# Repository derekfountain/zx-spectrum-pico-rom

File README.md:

# zx-spectrum-pico-rom

## A Pico-based switchable ROM interface for the ZX Spectrum

This is a ROM interface board for the ZX Spectrum. It presents a new,
selectable ROM image for the machine, replacing the 1982 BASIC one
found in the IC on the Spectrum's PCB.

There are lots of these around, all based on ROM and EEPROM chips. My
design is based on a Raspberry Pi Pico microcontroller programmed to
emulate a ROM chip.

The main advantage of doing it this way is that the Pico has enough
memory for several ROM images, and enough flash for as many ROMs as
anyone would likely ever want. A button allows the loaded ROMs to be
cycled.

It works like this (click through for YouTube video):

https://youtube.com/shorts/0Ot5mol2f5A?feature=share

Update Dec'24: I used this Pico ROM project as the basis for a bit
of experimentation with the Z80's non maskable interrupt (NMI) on 
the Spectrum. Updated software and description are [here](https://github.com/derekfountain/zx-spectrum-pico-rom/tree/main/firmware_nmi).
If you're after a simpler version of the Pico code to do a simple
ROM emulation task, that's probably the version you want.

Update Feb'25: I further used this Pico ROM project as the basis for adding a carefully timed non maskable interrupt (NMI) which fires each frame at the point the Spectrum is about to draw the lower border. Not sure how much value there is there, but if anyone's interested the subproject is [here](https://github.com/derekfountain/zx-spectrum-pico-rom/tree/main/firmware_nmi_lower_border).

## Design

The Z80's address and data bus lines are connected to the Pico's
GPIOs.  GPIOs are limited on the Pico (there's only 26), so only 14 of
the 16 address lines are connected. A bit of external logic handles the
top two. The software on the Pico sits spinning, watching for that logic
to indicate that A14, A15 and /MREQ are all zero, that being the indication
of a ZX Spectrum ROM memory access by the Z80. When that condition is
met the address the Z80 is requesting (in the range 0x0000 to 0x3FFF)
is found from the GPIOs connected to the address bus, and the value from
that offset in the currently enabled ROM image is fetched. The 8 bits of
that value are placed on the 8 GPIOs connected as outputs to the Z80's
data bus.

## Hardware design

The Spectrum is +5V, the Pico is 3V3, so every bus or signal pin needs
level shifting, down on the way into the Pico, up on the way out.

GPIO count is also pretty tight, which is why the external logic is
required. It's a simple 3-input OR gate which ORs A14, A15 and
/MREQ. The output of that gate is fed into the Pico, saving 2 GPIOs.

It's important that the device doesn't assert an output value onto the
Z80's data bus until it needs to. This is controlled by hardware. The
data bus level shifter is set permanently to the Pico->ZX direction,
but is left off (via its chip-enable line) until the ROM is being
read. The /CE line is pulled low by the output of the 3-way OR gate,
so when the Z80 is reading from ROM the level shifter is turned on and
the value on the data bus is connected to the Z80. As soon as the
/MREQ line goes high again the OR result goes true and the level shifter
is turned off again.

The Pico needs the ability to reset the Z80, which gets very unhappy if
the ROM program it's running is suddenly changed from underneath it. The
Z80's /RESET line is connected to a GPIO via a transistor; the line is
pulled low via Pico software when the Pico changes the ROM image in order
to reset the Z80.

There's a single user input button connected to the one remaining GPIO
on the Pico. In the current software this cycles the ROM to the next one
in the (compiled in) sequence. The Pico's ADC is available so more buttons
and a better user interface could be constructed using a resistor ladder.

The Z80's /M1 line is connected to a Pico GPIO input. This isn't required
for the typical use case, but it makes the device a useful test bed for
running the ZX Interface One ROM - see below.

### Caveat

Feb'25: I was playing around with one of these interfaces, and found myself
wanting to re-enable the Spectrum's ROM with the interface still plugged in.
(I needed the Pico for something, but with the Spectrum's own ROM.) So I
cut the /ROMCS track on the back of the interface, and then spent some time
trying to figure out why the Spectrum wasn't working.

Eventually it dawned on me: when I cut the track the Spectrum's ROM IC
was re-enabled, and it started to drive the data bus. But the U4 level
shifter was still working on the interface, which meant that was also driving
the data bus. That's a bad thing, the two ICs were both trying to be outputs
and were driving each other's data lines. The Z80 was getting garbage on the
data bus, and I think I was rather lucky nothing got damaged. I removed the
level shifter to complete my experimentation.

So, um, don't do that. :)

### Construction

The gerbers archive for upload, for example, JLCPCB, is
srom/fab1.2/fab1.2.zip. It's a simple 2 layer board.

Note: As of this writing I've not actually had one of these made. I
hand-modified my v1.1 board with the errata from v1.1. The v1.2 design
has had those modifications added so I'd expect it to work exactly the
same as my modified v1.1 board. But I haven't tried it yet. The switch,
in particular, might yet require another tweak depending on what
piece of hardware is chosen. I used a 6mm x 6mm right angle switch.

There's nothing complicated about the soldering. Do the big ICs first
and the Pico sockets, if you use them, last.

## Software Design

The software which runs on the Pico is built on a simple loop which
does this:

 * spin, waiting for the ROM-being-accessed signal to come in
 * read the 14 bits of the address bus from the GPIOs
 * convert that bit pattern into an offset
 * find the value of the byte at that offset into the currently
   used ROM image
 * apply the 8 bits of that byte value to the 8 output GPIOs connected
   to the Z80's data bus
 * go back to the top

The glaring issue here is speed. Pg8 of the Z80 manual says that the
timing for M1, the instruction fetch, is most time critical. The data
is sampled off the bus one and a half clocks after /MREQ goes low. On
the Spectrum's 3.5MHz Z80 that's 4.28571428571e-07 seconds, so about
430ns. Despite several efforts at optimisation I've been unable to get
the Pico to reliably return the data value inside that time frame. Much
to my frustration, v1.2 of the software still requires an overclock from
133MHz to 140MHz.

The Z80 starts up faster than the Pico which requires half a second or
so to get going. This means the Z80 is asking for ROM instructions 
before the Pico is ready to provide them. The Pico resets the Z80 as
soon as it, the Pico, is ready to go. That's why there's a colourful
display of randomness for a moment at startup.

## ROM Images

The device is permanently enabled; the original ROM chip in the
Spectrum is disabled while the interface is attached.

The Pico software contains the ROM images it's compiled with, the
first of which would typically be the original ZX ROM from 1982. I've
added a diagnostics ROM and the Gosh Wonderful ROM since they are free
to redistribute. Games ROMs are not included in the source release but
they can be added fairly easily. A Linux command like:

 xxd -i spaceraiders.rom

will convert a ROM image into 'C' array data which can be dropped into
roms.h.

### Switcher ROM

Some of the ROMs look superficially similar, like the original 1982
ROM and the Gosh Wonderful ROM. It got confusing trying to work out
what was running. I wanted a row of LEDs across the top of the device
to act as an indicator of which ROM was in use, but I didn't have any
GPIOs to implement it with. So I added an extra ROM image I called the
"switcher" ROM.

This program is written in 'C' and compiled with Z88DK. The source is
in the firmware/switcher directory. It presents a banner saying what ROM
is coming up next, then sits indefinitely buzzing the Spectrum's border.

")

When the user input button is pressed, the Pico software selects this
switcher ROM and resets the Z80 to start it running. The banner appears
on the Spectrum screen. About a second later an alarm goes off in the
Pico, the handler for which selects the next ROM in sequence and resets
the Z80 again. Thus the switcher ROM appears as a banner on the Spectrum
screen between each ROM switch.

## ZX Interface One

This device can also switch in and out the ZX Interface One's ROM. This
is an 8K ROM which, in the actual IF1, is paged in by hardware on 3 magic
address accesses: it's paged in when the Z80 requests an instruction from
addresses 0x0008 and 0x1708, and paged out again when the Z80 requests an
instruction from address 0x0700. It's early days with this idea, but that
boils down to this code:

    if( (rom_address == 0x0008) || (rom_address == 0x1708) )
    {
      rom_image_ptr = __ROMs_if1_rom;
    }
    else if( rom_address == 0x0700 )
    {
      rom_image_ptr = __ROMs_48_original_rom;
    }

This needs the /M1 input merged into the logic, but that's the
idea. The joys of programmable devices like the Pico, as opposed to
hardware. :)

There's a macro in the firmware source to switch in an early IF1 paging
version of the code. It seems unreliable, but I won't be persuing this
any further with this project.

Note: the v1.1 board doesn't have the /M1 signal connected. The v1.2
board has it connected into GPIO15. The software doesn't have the /M1
signal taken into account as yet.

## Bill of Materials

You will need:

3x [74LVC245 Bus transceiver](https://www.mouser.co.uk/ProductDetail/595-SN74LVC245ANSR)
Bus transceiver, used as a level shifter
<br>
1x [3216 SMD Diode](https://www.mouser.co.uk/ProductDetail/581-SD1206S040S2R0)
Schottky Diode for Pico input protection
<br>
1x [4075 OR gate](https://www.mouser.co.uk/ProductDetail/595-SN74HCS4075DR)
3-way 3-input OR gate
<br>
4x [3216 SMD 0.1uF capacitor](https://www.mouser.co.uk/ProductDetail/581-12065C104KAT4A)
Decoupling capacitor
<br>
1x [PMBT2222A SMD Transistor](https://www.mouser.co.uk/ProductDetail/771-PMBT2222A-T-R)
NPN Transistor for /RESET
<br>
1x [3216 SMD 1K Resistor](https://www.mouser.co.uk/ProductDetail/603-RT1206FRE071KL)
1K Resistor for /RESET

Also:

1x Raspberry Pi Pico with pins and sockets if you want them
<br>
1x ZX Spectrum Edge Connector socket
<br>
1x SPST switch any single pole, single throw switch to use as an input button. The footprint
on the board matches one I happen to have had, assume you'll add it on flying leads.

## Licence

Distributed as free software and hardware design under the GPL. The ROM
images have their own licences, see the ROMs/ directory.

Derek Fountain
February 2023

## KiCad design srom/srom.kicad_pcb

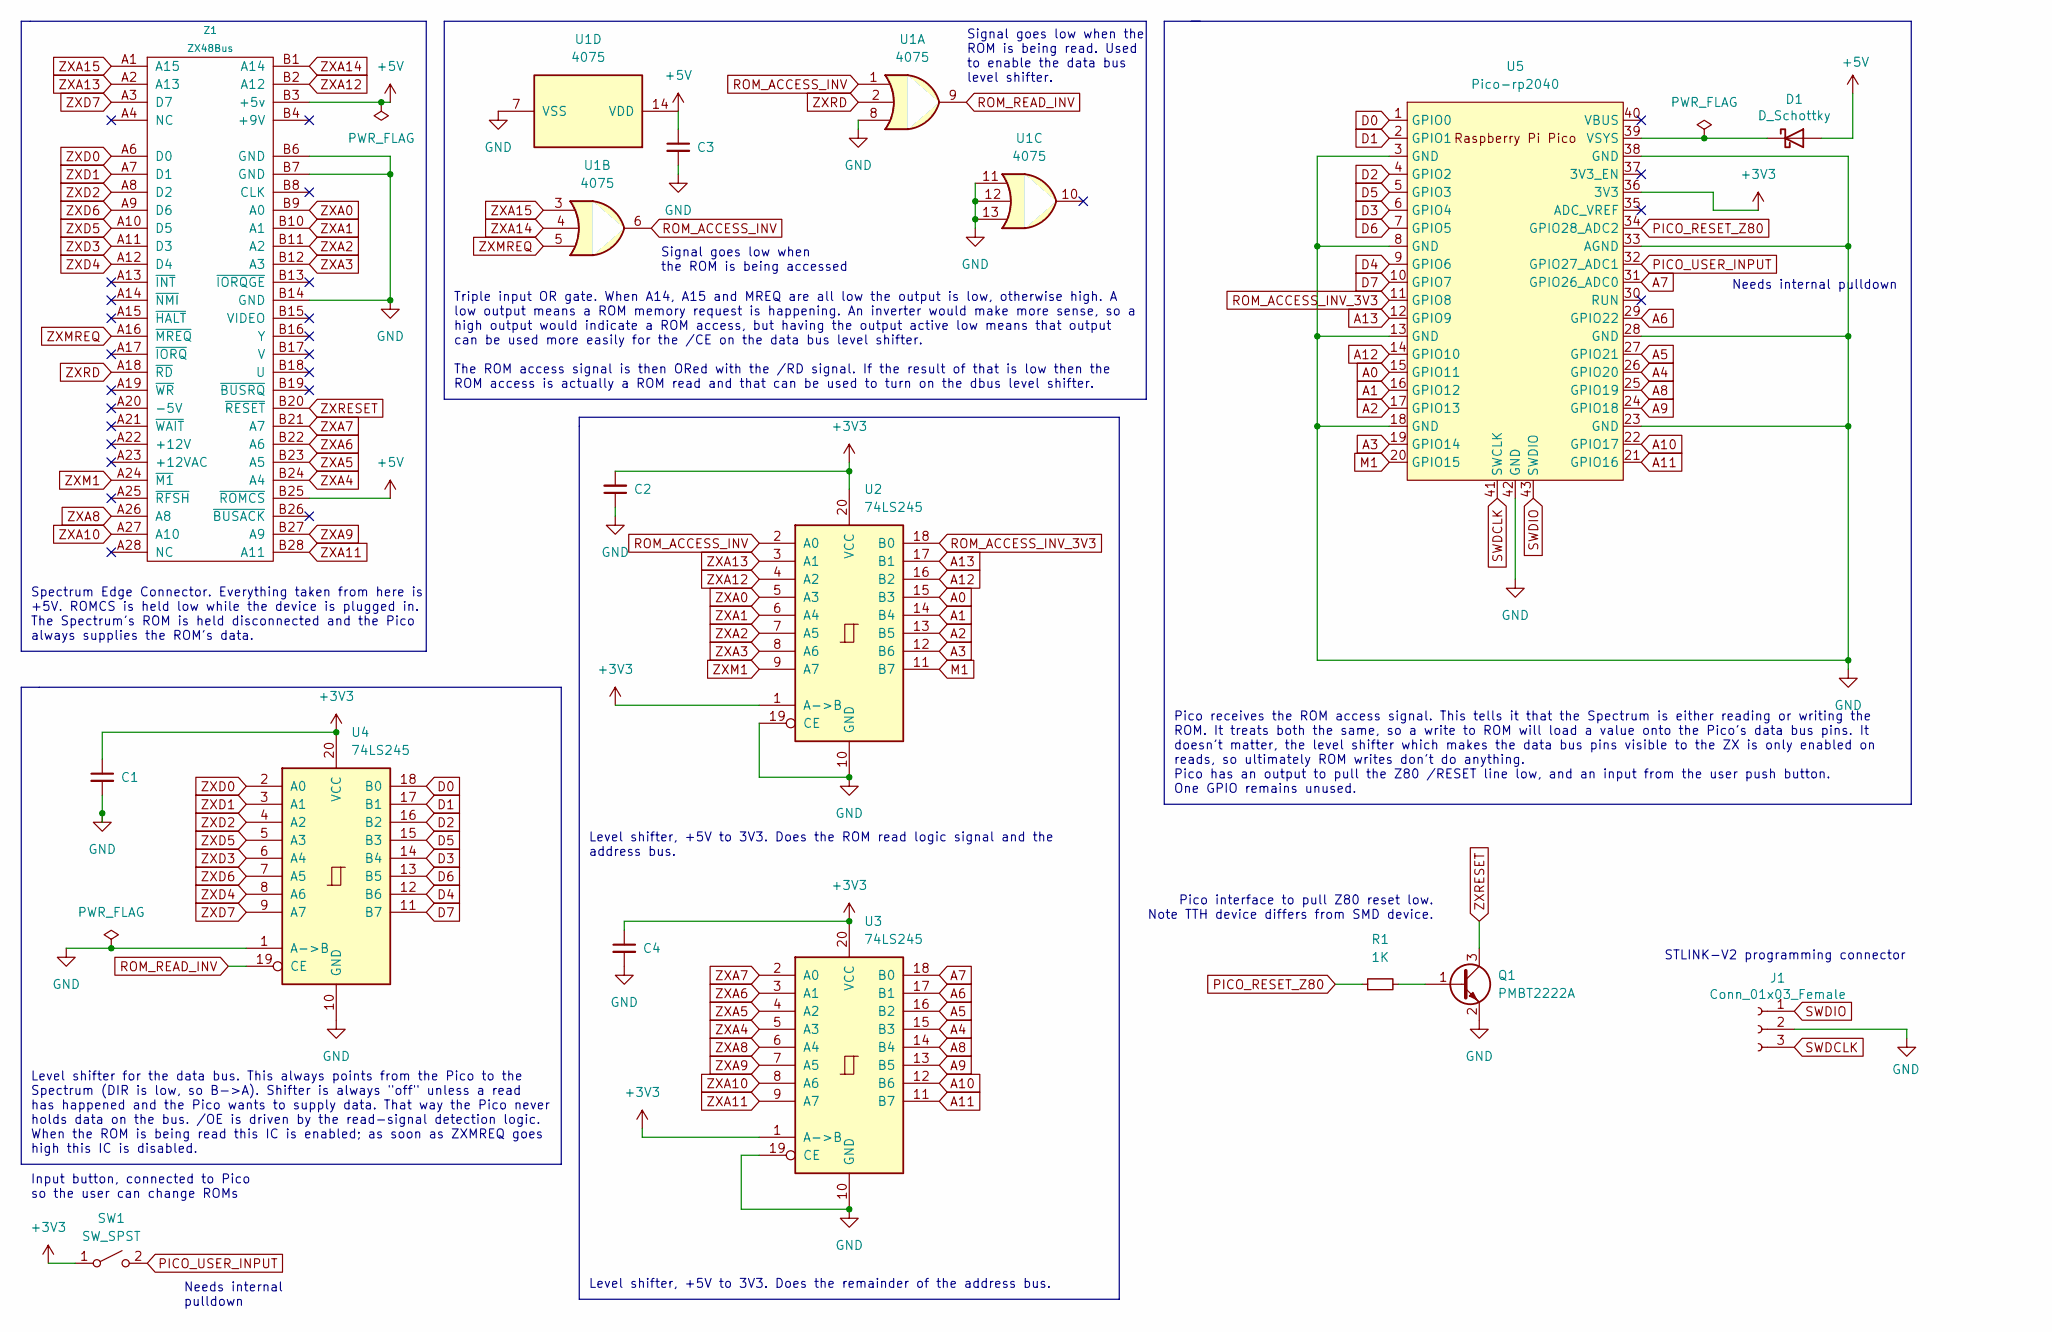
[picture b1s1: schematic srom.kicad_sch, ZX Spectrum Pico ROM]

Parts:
C1, C2, C3, C4: C_Small; C_1206_3216Metric
D1: D_Schottky; D_1206_3216Metric_Pad1.42x1.75mm_HandSolder
J1: Conn_01x03_Female; PinHeader_1x03_P2.54mm_Vertical
Q1: PMBT2222A; TSOT-23_HandSoldering
R1: 1K; R_1206_3216Metric_Pad1.30x1.75mm_HandSolder
SW1: SW_SPST; SW_Tactile_SKHH_Angled
U1: 4075; SOIC-14_3.9x8.7mm_P1.27mm
U2, U3, U4: 74LS245; SO-20_5.3x12.6mm_P1.27mm
U5: Pico-rp2040; RPi_Pico_SMD_TH
Z1: ZX48Bus; ZX_Bus_Pin_Header

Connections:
+3V3: C1.1, C2.2, C4.1, SW1.1 (A), U2.1 (A->B), U2.20 (VCC), U3.1 (A->B), U3.20 (VCC), U4.20 (VCC), U5.36 (3V3)
+5V: C3.1, D1.2 (A), U1.14 (VDD), Z1.B3 (+5v), Z1.B25 (~ROMCS)
A0: U2.15 (B3), U5.15 (GPIO11)
A1: U2.14 (B4), U5.16 (GPIO12)
A2: U2.13 (B5), U5.17 (GPIO13)
A3: U2.12 (B6), U5.19 (GPIO14)
A4: U3.15 (B3), U5.26 (GPIO20)
A5: U3.16 (B2), U5.27 (GPIO21)
A6: U3.17 (B1), U5.29 (GPIO22)
A7: U3.18 (B0), U5.31 (GPIO26_ADC0)
A8: U3.14 (B4), U5.25 (GPIO19)
A9: U3.13 (B5), U5.24 (GPIO18)
A10: U3.12 (B6), U5.22 (GPIO17)
A11: U3.11 (B7), U5.21 (GPIO16)
A12: U2.16 (B2), U5.14 (GPIO10)
A13: U2.17 (B1), U5.12 (GPIO9)
D0: U4.18 (B0), U5.1 (GPIO0)
D1: U4.17 (B1), U5.2 (GPIO1)
D2: U4.16 (B2), U5.4 (GPIO2)
D3: U4.14 (B4), U5.6 (GPIO4)
D4: U4.12 (B6), U5.9 (GPIO6)
D5: U4.15 (B3), U5.5 (GPIO3)
D6: U4.13 (B5), U5.7 (GPIO5)
D7: U4.11 (B7), U5.10 (GPIO7)
GND: C1.2, C2.1, C3.2, C4.2, J1.2, Q1.2 (E), U1.7 (VSS), U1.8, U1.11, U1.12, U1.13, U2.10 (GND), U2.19 (CE), U3.10 (GND), U3.19 (CE), U4.1 (A->B), U4.10 (GND), U5.3 (GND), U5.8 (GND), U5.13 (GND), U5.18 (GND), U5.23 (GND), U5.28 (GND), U5.33 (AGND), U5.38 (GND), U5.42 (GND), Z1.B6 (GND), Z1.B7 (GND), Z1.B14 (GND)
M1: U2.11 (B7), U5.20 (GPIO15)
unnamed: D1.1 (K), U5.39 (VSYS)
unnamed: Q1.1 (B), R1.2
PICO_RESET_Z80: R1.1, U5.34 (GPIO28_ADC2)
PICO_USER_INPUT: SW1.2 (B), U5.32 (GPIO27_ADC1)
ROM_ACCESS_INV: U1.1, U1.6, U2.2 (A0)
ROM_ACCESS_INV_3V3: U2.18 (B0), U5.11 (GPIO8)
ROM_READ_INV: U1.9, U4.19 (CE)
SWDCLK: J1.3, U5.41 (SWCLK)
SWDIO: J1.1, U5.43 (SWDIO)
ZXA0: U2.5 (A3), Z1.B9 (A0)
ZXA1: U2.6 (A4), Z1.B10 (A1)
ZXA2: U2.7 (A5), Z1.B11 (A2)
ZXA3: U2.8 (A6), Z1.B12 (A3)
ZXA4: U3.5 (A3), Z1.B24 (A4)
ZXA5: U3.4 (A2), Z1.B23 (A5)
ZXA6: U3.3 (A1), Z1.B22 (A6)
ZXA7: U3.2 (A0), Z1.B21 (A7)
ZXA8: U3.6 (A4), Z1.A26 (A8)
ZXA9: U3.7 (A5), Z1.B27 (A9)
ZXA10: U3.8 (A6), Z1.A27 (A10)
ZXA11: U3.9 (A7), Z1.B28 (A11)
ZXA12: U2.4 (A2), Z1.B2 (A12)
ZXA13: U2.3 (A1), Z1.A2 (A13)
ZXA14: U1.4, Z1.B1 (A14)
ZXA15: U1.3, Z1.A1 (A15)
ZXD0: U4.2 (A0), Z1.A6 (D0)
ZXD1: U4.3 (A1), Z1.A7 (D1)
ZXD2: U4.4 (A2), Z1.A8 (D2)
ZXD3: U4.6 (A4), Z1.A11 (D3)
ZXD4: U4.8 (A6), Z1.A12 (D4)
ZXD5: U4.5 (A3), Z1.A10 (D5)
ZXD6: U4.7 (A5), Z1.A9 (D6)
ZXD7: U4.9 (A7), Z1.A3 (D7)
ZXM1: U2.9 (A7), Z1.A24 (~M1)
ZXMREQ: U1.5, Z1.A16 (~MREQ)
ZXRD: U1.2, Z1.A18 (~RD)
ZXRESET: Q1.3 (C), Z1.B20 (~RESET)

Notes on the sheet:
Needs internal pulldown
Level shifter, +5V to 3V3. Does the remainder of the address bus.
Level shifter, +5V to 3V3. Does the ROM read logic signal and the address bus.
Pico receives the ROM access signal. This tells it that the Spectrum is either reading or writing the ROM. It treats both the same, so a write to ROM will load a value onto the Pico's data bus pins. It doesn't matter, the level shifter which makes the data bus pins visible to the ZX is only enabled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
Needs internal pulldown
Level shifter for the data bus. This always points from the Pico to the Spectrum (DIR is low, so B->A). Shifter is always "off" unless a read has happened and the Pico wants to supply data. That way the Pico never holds data on the bus. /OE is driven by the read-signal detection logic. When the ROM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
Triple input OR gate. When A14, A15 and MREQ are all low the output is low, otherwise high. A low output means a ROM memory request is happening. An inverter would make more sense, so a high output would indicate a ROM access, but having the output active low means that output can be used more easi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
Pico interface to pull Z80 reset low. Note TTH device differs from SMD device.
Signal goes low when the ROM is being read. Used to enable the data bus level shifter.
Spectrum Edge Connector. Everything taken from here is +5V. ROMCS is held low while the device is plugged in. The Spectrum's ROM is held disconnected and the Pico always supplies the ROM's data.
Input button, connected to Pico so the user can change ROMs
Signal goes low when the ROM is being accessed
STLINK-V2 programming connector

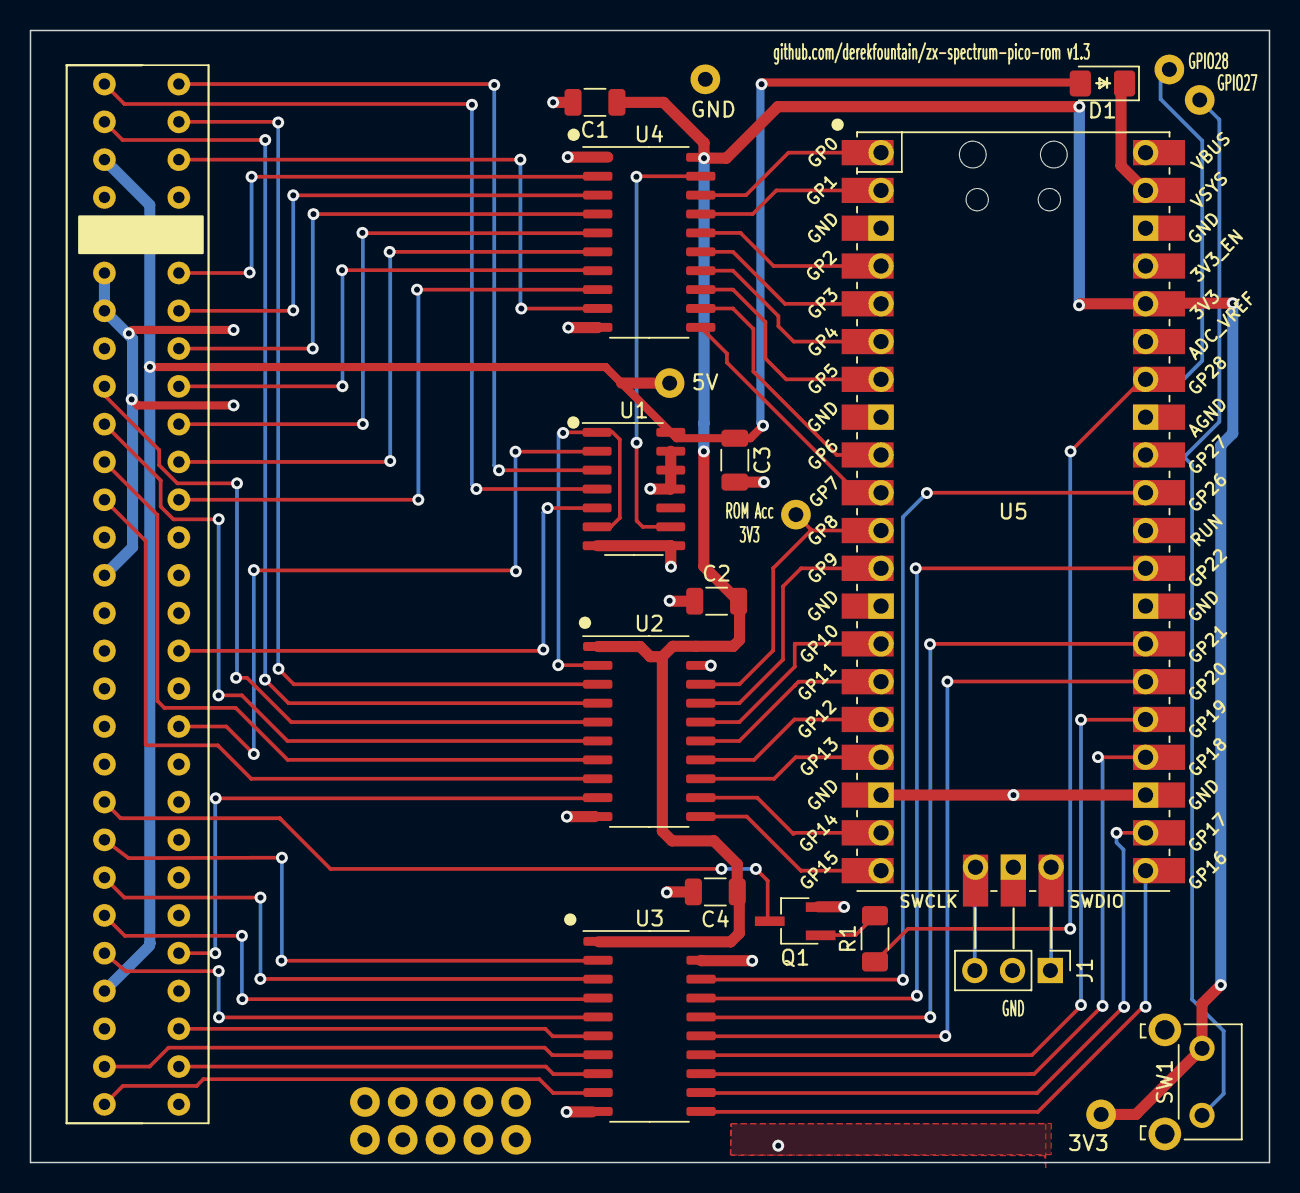
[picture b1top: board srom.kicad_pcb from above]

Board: 2 copper layers, 83.3 x 76.1 mm, 27 parts (0 on the bottom side), 63 nets.

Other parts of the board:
5, 6, 7, 8, 9, 10, 11, 12, 13, 14, 14#2, 14#3: (no value)

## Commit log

2023-01-01 initial
2023-01-01 fix error on pico input, it needs to know about any access, not just reads
2023-01-03 first effort at a layout
2023-01-03 minor updates to layout
2023-01-03 fab1.0 ready to go
2023-01-03 add notebook.txt file
2023-01-18 fix a couple of footprint errors with v1.0
2023-01-19 start on firmware, timings look ok with overclock, not working though
2023-01-19 first working version
2023-01-20 obvious optimisation, now runs at 250MHz with the /WR check in place
2023-01-20 try the address value optimisation, doesn't work, probably too complex to bother with. i'll take it out again
2023-01-20 add roms creation script
2023-01-24 hardware mod to add reset feature
2023-01-24 tidy up, trying to work out the issue i've introduced
2023-01-26 new hardware, now working, sort out ROM images
2023-01-27 periodic z80 reset test code, needs to come out but worth keeping
2023-01-28 reset button working, first version
2023-01-28 preconvert all rom images; rom switch button almost working
2023-01-28 settle on 4 ROM images in the header file
2023-01-28 rom switching appears to work
2023-01-28 rom switching now working
2023-01-29 finalise v1.1 schematic
2023-01-29 update pcb with errata
2023-01-29 add a ground plane on the back
2023-01-30 fab1.1 off for fabrication
2023-01-30 increase debounce time, microswitches are very noisy
2023-01-30 first address bus decode optimisation working
2023-01-30 tidy up address bus optimisation code
2023-01-30 final address bus tweak, overclock removed at least for now
2023-01-31 switcher ROM starts
2023-01-31 oops, remove switcher compiler junk properly
2023-01-31 change example to rolling border, link in ZX lib
2023-01-31 border effect rom in the main code, works on hardware
2023-01-31 banner in place
2023-01-31 basic rom switcher working
2023-01-31 clean up rom switcher, but i've gone wrong, need to back this out
2023-01-31 switcher rom appears correct now
2023-02-02 interface one version working with conditional compilation
2023-02-03 small tidy ups; the if1 instability is because i don't have /M1 going into the algorithm
2023-02-06 Add the /M1 line into the Pico so the IF1 ROM can be used
2023-02-06 Tidy IF1 ROM switching, works intermittently given there's no /M1 signal
2023-02-15 v1.2 schematic and layout complete
2023-02-16 there's a race in switcher code, tidy up with alarms, better but i think it's still there
2023-02-16 YT link in the readme, UF2 image added
2023-02-16 prepare v1.2, bit more to do yet
2023-02-16 updates to readme
2023-02-16 add images for readme
2023-02-22 add BOM to README
2023-02-22 small updates to readme and errata relating to M1 signal
2024-04-26 update readme with corrected level shifter name
2024-08-01 add v1.2 gerbers
2024-12-14 create v1.3 pcb with switch casing grounded, circuit is unchanged. kicad v8 automatic update at this point
2024-12-14 fix ROM NMI bug. fix button debounce
2024-12-15 tidy up the debounce, set the overclock higher as that's now required
2024-12-15 start NMI documentation
2024-12-15 add NMI subproject documentation
2024-12-17 add lower border nmi code
2025-01-27 pio timing loop appears to be correct now
2025-01-27 update comments in lower border NMI code
2025-01-27 add some images from the scope
2025-01-30 update lower border test, hardware issues resolved, picking this up again
2025-02-04 add caveat warning to README about re-enabling ZX ROM
2025-02-04 pulled code apart, put it all back together, checked hardware, zx still hangs :(
2025-02-04 dual core version fires NMI every 3secs, seems ok
2025-02-04 dual core version fires NMI every 20ms, unsynced to /INT but otherwise seems ok
2025-02-06 tidy up timers, start NMI at ZX boot time, glitching seems to have gone
2025-02-07 PIO working with a handler in ROM consisting of RETN
2025-02-07 finally, border change on NMI working reliably from PIO :)
2025-02-08 update documentation for the lower border version
